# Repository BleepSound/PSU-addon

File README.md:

[![CC BY-SA 4.0][cc-by-sa-shield]][cc-by-sa]

# PSU addon

Latest documentation available at https://bleepsound.github.io/modules/

This work is licensed under a
[Creative Commons Attribution-ShareAlike 4.0 International License][cc-by-sa].

[![CC BY-SA 4.0][cc-by-sa-image]][cc-by-sa]

[cc-by-sa]: http://creativecommons.org/licenses/by-sa/4.0/
[cc-by-sa-image]: https://licensebuttons.net/l/by-sa/4.0/88x31.png
[cc-by-sa-shield]: https://img.shields.io/badge/License-CC%20BY--SA%204.0-lightgrey.svg

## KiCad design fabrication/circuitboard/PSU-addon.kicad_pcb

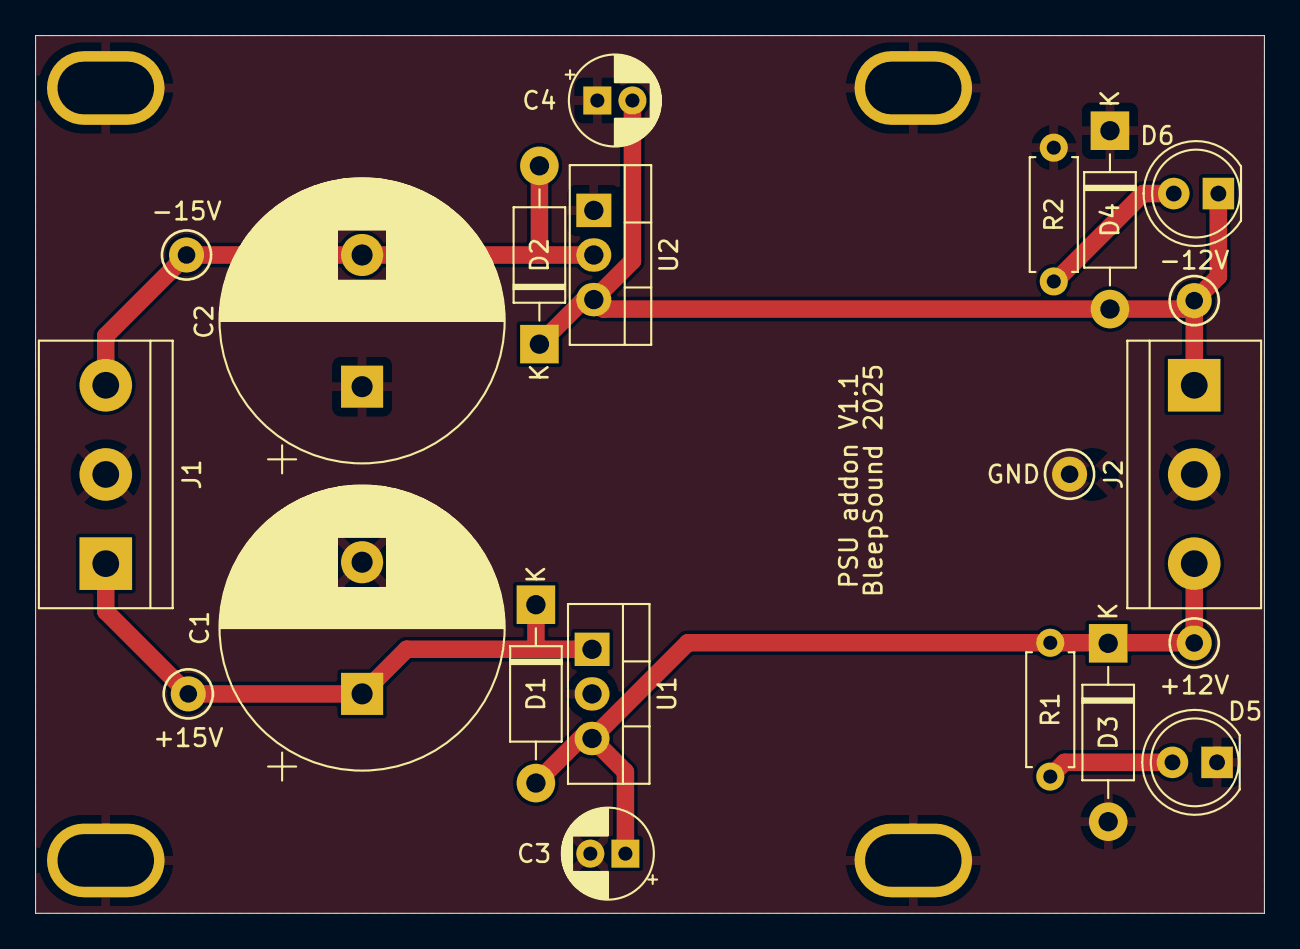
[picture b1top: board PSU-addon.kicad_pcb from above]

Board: 2 copper layers, 70.0 x 50.0 mm, 25 parts (0 on the bottom side), 7 nets.

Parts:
C1, C2: 4700µF; CP_Radial_D16.0mm_P7.50mm
C3, C4: 100µF; CP_Radial_D5.0mm_P2.00mm
D1, D2, D3, D4: 1N4004; D_DO-41_SOD81_P10.16mm_Horizontal
D5, D6: LED; LED_D5.0mm_Clear
H1, H2, H3, H4: MountingHole_Pad; Doepfer Mounting hole
J1, J2: Power output; TerminalBlock_bornier-3_P5.08mm
R1, R2: 2.2k; R_Axial_DIN0207_L6.3mm_D2.5mm_P7.62mm_Horizontal
TP1: +15V; TestPoint_Keystone_5000-5004_Miniature
TP2: -15V; TestPoint_Keystone_5000-5004_Miniature
TP3: +12V; TestPoint_Keystone_5000-5004_Miniature
TP4: GND; TestPoint_Keystone_5000-5004_Miniature
TP5: -12V; TestPoint_Keystone_5000-5004_Miniature
U1: L7812; TO-220-3_Vertical
U2: L7912; TO-220-3_Vertical

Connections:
GND: C1.2, C2.1, C3.2, C4.1, D3.2 (A), D4.1 (K), D5.1 (K), H1.1, H2.1, H3.1, H4.1, J1.2, J2.2, R2.2, TP4.1, U1.2 (GND), U2.1 (GND)
unnamed: C3.1, D1.2 (A), D3.1 (K), J2.3, R1.2, TP3.1, U1.3 (OUT)
unnamed: C1.1, D1.1 (K), J1.1, TP1.1, U1.1 (IN)
unnamed: C2.2, D2.2 (A), J1.3, TP2.1, U2.2 (VI)
unnamed: C4.2, D2.1 (K), D4.2 (A), D6.1 (K), J2.1, TP5.1, U2.3 (VO)
unnamed: D5.2 (A), R1.1
unnamed: D6.2 (A), R2.1

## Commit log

2025-01-21 V1.1
2025-11-27 add licence
